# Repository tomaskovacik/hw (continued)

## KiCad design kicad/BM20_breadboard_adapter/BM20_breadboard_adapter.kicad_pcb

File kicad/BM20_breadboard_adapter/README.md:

This is directory with whole kicad project files for breadboard adapter for BM20 and BM62 bluetooth modules from Microchip

<a href="https://tomaskovacik.github.io/hw/kicad/BM20_breadboard_adapter/bom/ibom.html">interactive boom</a>

assembled or bare boards can be found on my tindie store:

<a href="https://github.com/tomaskovacik/IS2020/wiki/Upgrading-firmware-on-BM62">wiki page</a> talking about upgrading firmware on BM62 module.

<a href="https://github.com/tomaskovacik/IS2020">Arduino library</a> for this module is also available as opensource project on GitHub.

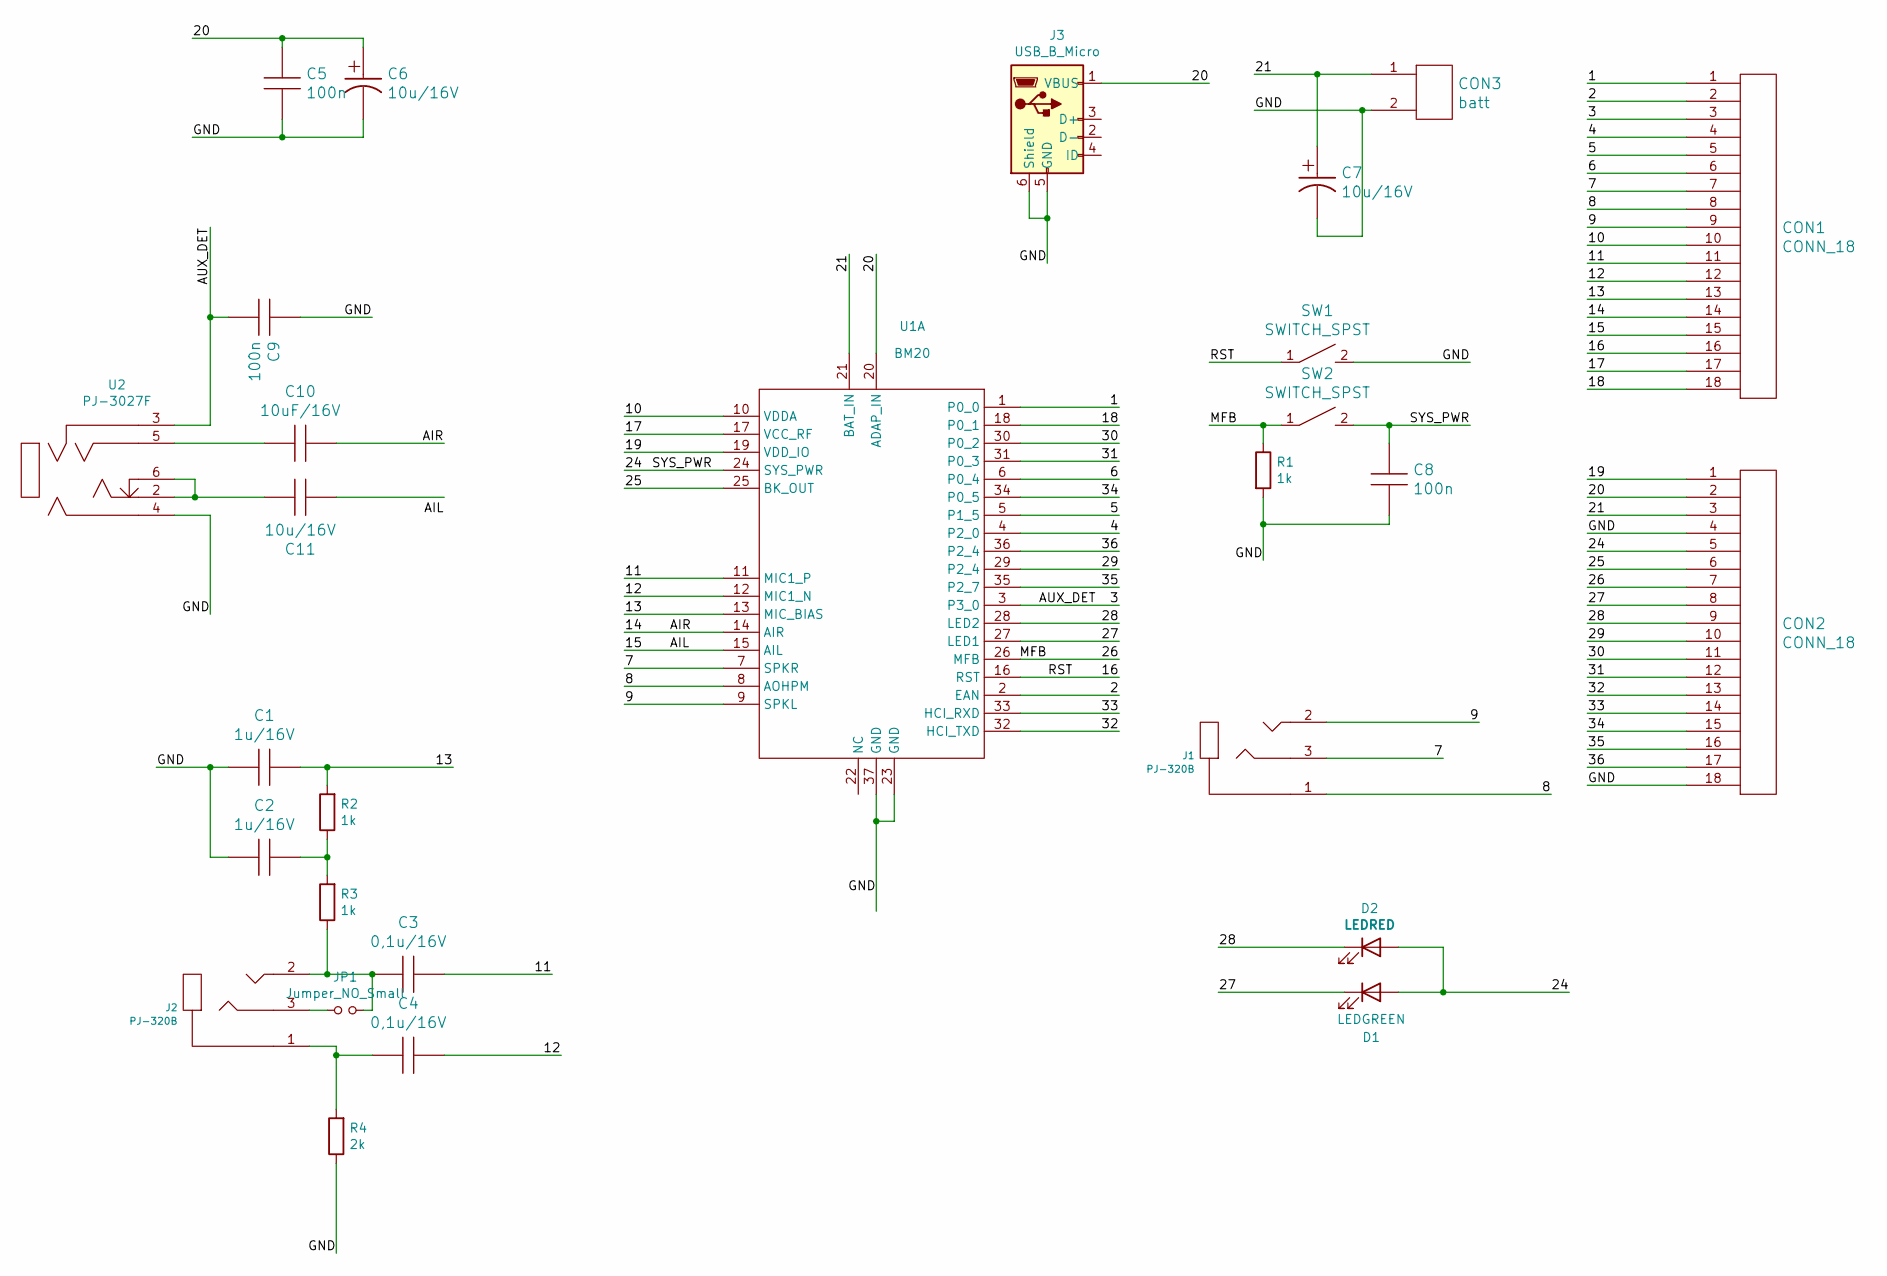
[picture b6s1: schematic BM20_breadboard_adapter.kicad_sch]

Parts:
C1, C2: 1u/16V; C_1206_HandSoldering
C3, C4: 0,1u/16V; C_1206_HandSoldering
C5, C8, C9: 100n; C_0805_HandSoldering
C6, C7, C11: 10u/16V; C_1206_HandSoldering
C10: 10uF/16V; C_1206_HandSoldering
CON1, CON2: CONN_18; Pin_Header_Straight_1x18
CON3: batt; JST_XH_B02B-XH-A_02x2.50mm_Straight
D1: LEDGREEN; LED_1206_HandSoldering
D2: LEDRED; LED_1206_HandSoldering
J1, J2: PJ-320B; 3.5mm_stereo_jack_PJ320B
J3: USB_B_Micro; USB_Micro-B
JP1: Jumper_NO_Small; SolderJumper-2_P1.3mm_Open_RoundedPad1.0x1.5mm
R1, R2, R3: 1k; R_0805_HandSoldering
R4: 2k; R_0805_HandSoldering
SW1, SW2: SWITCH_SPST; SW_SPST_FSMSM
U1: BM20; BM20_no_silk_screen_under_antena
U2: PJ-3027F; PJ-327A

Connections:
/1: CON1.1, U1.1 (P0_0)
/2: CON1.2, U1.2 (EAN)
/3: C9.2, CON1.3, U1.3 (P3_0), U2.3
/4: CON1.4, U1.4 (P2_0)
/5: CON1.5, U1.5 (P1_5)
/6: CON1.6, U1.6 (P0_4)
/7: CON1.7, J1.3, U1.7 (SPKR)
/8: CON1.8, J1.1, U1.8 (AOHPM)
/9: CON1.9, J1.2, U1.9 (SPKL)
/10: CON1.10, U1.10 (VDDA)
/11: C3.1, CON1.11, U1.11 (MIC1_P)
/12: C4.1, CON1.12, U1.12 (MIC1_N)
/13: C1.1, CON1.13, R2.2, U1.13 (MIC_BIAS)
/14: C10.1, CON1.14, U1.14 (AIR)
/15: CON1.15, U1.15 (AIL)
/16: CON1.16, SW1.1, U1.16 (RST)
/17: CON1.17, U1.17 (VCC_RF)
/18: CON1.18, U1.18 (P0_1)
/19: CON2.1, U1.19 (VDD_IO)
/20: C5.1, C6.1, CON2.2, J3.1 (VBUS), U1.20 (ADAP_IN)
/21: C7.1, CON2.3, CON3.1, U1.21 (BAT_IN)
/24: C8.1, CON2.5, D1.2 (A), D2.2 (A), SW2.2, U1.24 (SYS_PWR)
/25: CON2.6, U1.25 (BK_OUT)
/26: CON2.7, R1.1, SW2.1, U1.26 (MFB)
/27: CON2.8, D1.1 (K), U1.27 (LED1)
/28: CON2.9, D2.1 (K), U1.28 (LED2)
/29: CON2.10, U1.29 (P2_4)
/30: CON2.11, U1.30 (P0_2)
/31: CON2.12, U1.31 (P0_3)
/32: CON2.13, U1.32 (HCI_TXD)
/33: CON2.14, U1.33 (HCI_RXD)
/34: CON2.15, U1.34 (P0_5)
/35: CON2.16, U1.35 (P2_7)
/36: CON2.17, U1.36 (P2_4)
/GND: C1.2, C2.2, C5.2, C6.2, C7.2, C8.2, C9.1, CON2.4, CON2.18, CON3.2, J3.5 (GND), J3.6 (Shield), R1.2, R4.1, SW1.2, U1.23 (GND), U1.37 (GND), U2.4
unnamed: C2.1, R2.1, R3.2
unnamed: C3.2, J2.2, JP1.2, R3.1
unnamed: C4.2, J2.1, R4.2
unnamed: C10.2, U2.5
unnamed: C11.1, U2.2, U2.6
unnamed: J2.3, JP1.1

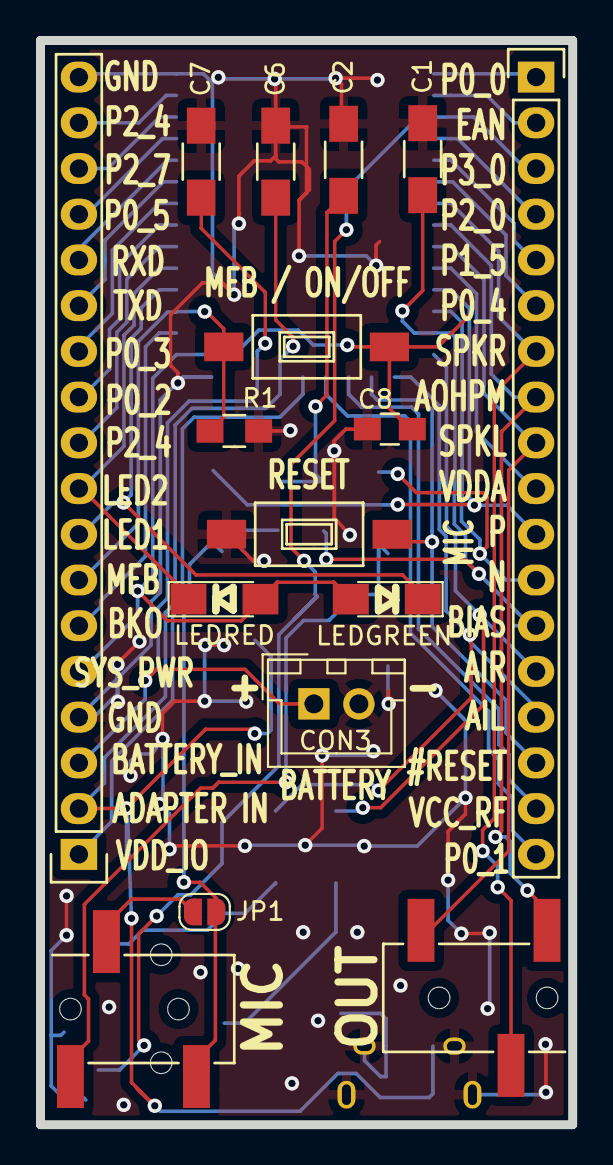
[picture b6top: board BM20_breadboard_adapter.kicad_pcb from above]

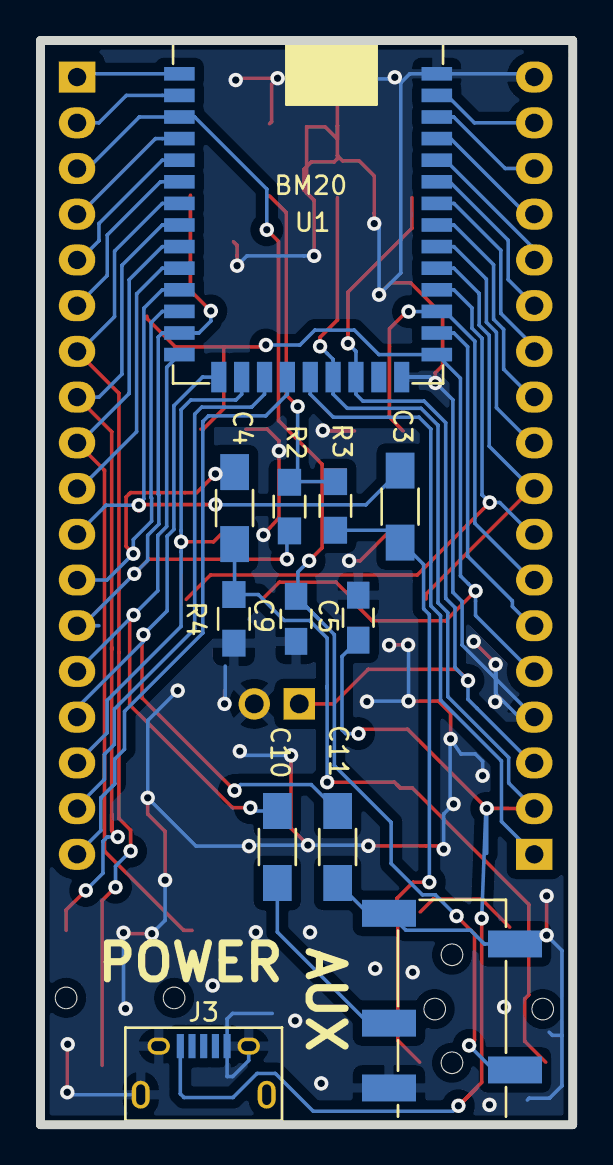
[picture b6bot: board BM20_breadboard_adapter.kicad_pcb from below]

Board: 2 copper layers, 29.6 x 60.2 mm, 28 parts (12 on the bottom side), 41 nets.

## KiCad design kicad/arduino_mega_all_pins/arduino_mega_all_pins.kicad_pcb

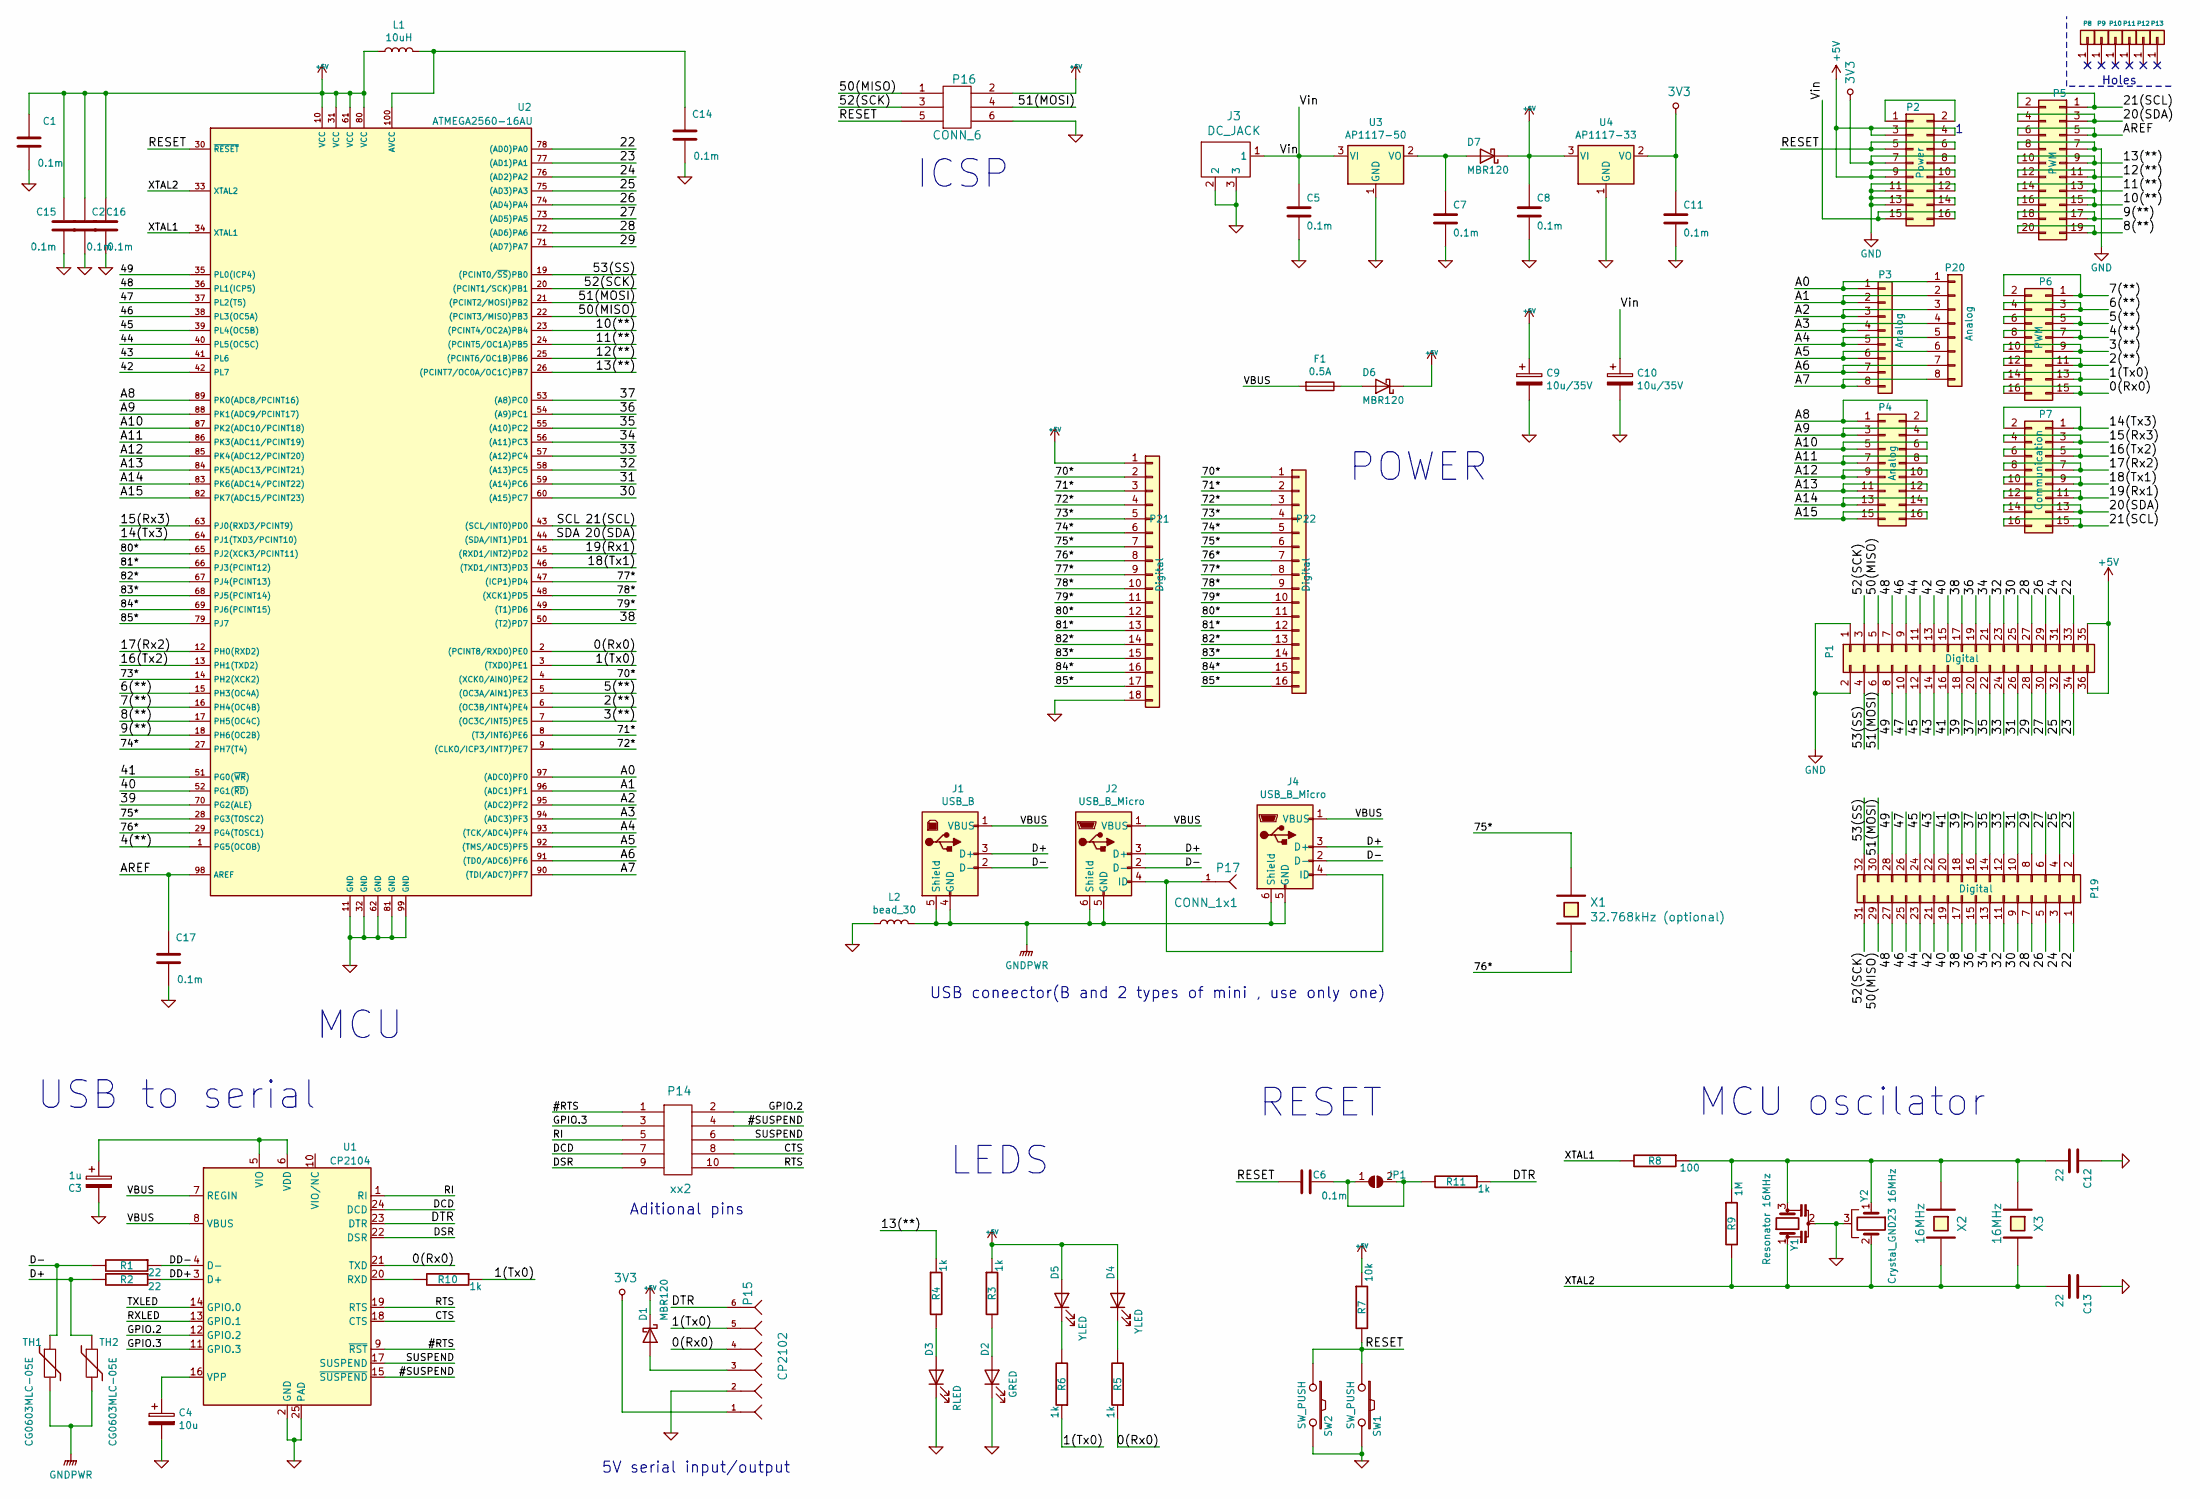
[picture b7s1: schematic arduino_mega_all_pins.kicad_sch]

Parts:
C1, C2, C5, C6, C7, C8, C11, C14, C15, C16, C17: 0.1m; C_0805_HandSoldering
C3: 1u; TantalC_SizeA_EIA-3216_Wave
C4: 10u; TantalC_SizeA_EIA-3216_Wave
C9, C10: 10u/35V; TantalC_SizeD_EIA-7343_Wave
C12, C13: 22; C_0805_HandSoldering
D1, D6, D7: MBR120; SOD-123
D2: GRED; LED-1206
D3: RLED; LED-1206
D4, D5: YLED; LED-1206
F1: 0.5A; Fuse_SMD1206_Wave
J1: USB_B
J2: USB_B_Micro; USB_Micro-B
J3: DC_JACK; JACK_ALIM
J4: USB_B_Micro; AB2_USB_MICRO_SMD
JP1: SolderJumper_2_Bridged; SolderJumper-2_P1.3mm_Open_RoundedPad1.0x1.5mm
L1: 10uH; Choke_SMD_1206_Standard
L2: bead_30; Choke_SMD_1206_Standard
P1: Digital; Socket_Strip_Arduino_2x18
P2: Power; Pin_Header_Straight_2x08
P3, P20: Analog; Pin_Header_Straight_1x08
P4: Analog; Pin_Header_Straight_2x08
P5: PWM; Pin_Header_Straight_2x10
P6: PWM; Pin_Header_Straight_2x08
P7: Communication; Pin_Header_Straight_2x08
P8, P9, P10, P11, P12, P13: CONN_01X01; Arduino_1pin
P14: xx2; Pin_Header_Straight_2x05
P15: CP2102; Pin_Header_Straight_1x06
P16: CONN_6; Pin_Header_Straight_2x03
P17: CONN_1x1; Pin_Header_Straight_1x01
P19: Digital; Pin_Header_Straight_2x16
P21: Digital; Pin_Header_Straight_1x18
P22: Digital; Pin_Header_Straight_1x16
R1, R2: 22; R_0805_HandSoldering
R3, R4, R5, R6, R10, R11: 1k; R_0805_HandSoldering
R7: 10k; R_0805_HandSoldering
R8: 100; R_0805_HandSoldering
R9: 1M; R_0805_HandSoldering
SW1, SW2: SW_PUSH; 3x6x2.5mm_tact_switch
TH1, TH2: CG0603MLC-05E; R_0603_HandSoldering
U1: CP2104; QFN-24-1EP_4x4mm_Pitch0.5mm
U2: ATMEGA2560-16AU; TQFP-100_14x14mm_Pitch0.5mm
U3: AP1117-50; AB2_SOT223
U4: AP1117-33; AB2_SOT223
X1: 32.768kHz (optional); Crystal_Round_Horizontal_3mm_BigPad
X2: 16MHz; Crystal_HC49-U_Vertical
X3: 16MHz; Q_49U3HMS
Y1: Resonator 16MHz; MURATA_CSTCE_V53
Y2: Crystal_GND23 16MHz; CRYSTAL_3225

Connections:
3V3: C11.1, P2.7, P2.8, P15.1, U4.2 (VO)
+5V: C1.2, C2.2, C8.1, C9.1, C15.2, C16.2, D1.1 (K), D4.2 (A), D5.2 (A), D6.1 (K), D7.1 (K), L1.1, P1.35, P1.36, P2.3, P2.4, P2.9, P2.10, P16.2, P21.1, R3.1, R7.1, U2.10 (VCC), U2.31 (VCC), U2.61 (VCC), U2.80 (VCC), U4.3 (VI)
/0(Rx0): P6.15, P6.16, P15.4, R5.1, U1.21 (TXD), U2.2 ((PCINT8/RXD0)PE0)
/1(Tx0): P6.13, P6.14, P15.5, R6.1, R10.1, U2.3 ((TXD0)PE1)
/2(**): P6.11, P6.12, U2.6 ((OC3B/INT4)PE4)
/3(**): P6.9, P6.10, U2.7 ((OC3C/INT5)PE5)
/4(**): P6.7, P6.8, U2.1 (PG5(OCOB))
/5(**): P6.5, P6.6, U2.5 ((OC3A/AIN1)PE3)
/6(**): P6.3, P6.4, U2.15 (PH3(OC4A))
/7(**): P6.1, P6.2, U2.16 (PH4(OC4B))
/8(**): P5.19, P5.20, U2.17 (PH5(OC4C))
/9(**): P5.17, P5.18, U2.18 (PH6(OC2B))
/10(**): P5.15, P5.16, U2.23 ((PCINT4/OC2A)PB4)
/11(**): P5.13, P5.14, U2.24 ((PCINT5/OC1A)PB5)
/12(**): P5.11, P5.12, U2.25 ((PCINT6/OC1B)PB6)
/13(**): P5.9, P5.10, R4.1, U2.26 ((PCINT7/OC0A/OC1C)PB7)
/14(Tx3): P7.1, P7.2, U2.64 (PJ1(TXD3/PCINT10))
/15(Rx3): P7.3, P7.4, U2.63 (PJ0(RXD3/PCINT9))
/16(Tx2): P7.5, P7.6, U2.13 (PH1(TXD2))
/17(Rx2): P7.7, P7.8, U2.12 (PH0(RXD2))
/18(Tx1): P7.9, P7.10, U2.46 ((TXD1/INT3)PD3)
/19(Rx1): P7.11, P7.12, U2.45 ((RXD1/INT2)PD2)
/20(SDA): P5.3, P5.4, P7.13, P7.14, U2.44 ((SDA/INT1)PD1)
/21(SCL): P5.1, P5.2, P7.15, P7.16, U2.43 ((SCL/INT0)PD0)
/22: P1.33, P19.1, U2.78 ((AD0)PA0)
/23: P1.34, P19.2, U2.77 ((AD1)PA1)
/24: P1.31, P19.3, U2.76 ((AD2)PA2)
/25: P1.32, P19.4, U2.75 ((AD3)PA3)
/26: P1.29, P19.5, U2.74 ((AD4)PA4)
/27: P1.30, P19.6, U2.73 ((AD5)PA5)
/28: P1.27, P19.7, U2.72 ((AD6)PA6)
/29: P1.28, P19.8, U2.71 ((AD7)PA7)
/30: P1.25, P19.9, U2.60 ((A15)PC7)
/31: P1.26, P19.10, U2.59 ((A14)PC6)
/32: P1.23, P19.11, U2.58 ((A13)PC5)
/33: P1.24, P19.12, U2.57 ((A12)PC4)
/34: P1.21, P19.13, U2.56 ((A11)PC3)
/35: P1.22, P19.14, U2.55 ((A10)PC2)
/36: P1.19, P19.15, U2.54 ((A9)PC1)
/37: P1.20, P19.16, U2.53 ((A8)PC0)
/38: P1.17, P19.17, U2.50 ((T2)PD7)
/39: P1.18, P19.18, U2.70 (PG2(ALE))
/40: P1.15, P19.19, U2.52 (PG1(~RD~))
/41: P1.16, P19.20, U2.51 (PG0(~WR~))
/42: P1.13, P19.21, U2.42 (PL7)
/43: P1.14, P19.22, U2.41 (PL6)
/44: P1.11, P19.23, U2.40 (PL5(OC5C))
/45: P1.12, P19.24, U2.39 (PL4(OC5B))
/46: P1.9, P19.25, U2.38 (PL3(OC5A))
/47: P1.10, P19.26, U2.37 (PL2(T5))
/48: P1.7, P19.27, U2.36 (PL1(ICP5))
/49: P1.8, P19.28, U2.35 (PL0(ICP4))
/50(MISO): P1.5, P16.1, P19.29, U2.22 ((PCINT3/MISO)PB3)
/51(MOSI): P1.6, P16.4, P19.30, U2.21 ((PCINT2/MOSI)PB2)
/52(SCK): P1.3, P16.3, P19.31, U2.20 ((PCINT1/SCK)PB1)
/53(SS): P1.4, P19.32, U2.19 ((PCINT0/~SS~)PB0)
/70*: P21.2, P22.1, U2.4 ((XCK0/AIN0)PE2)
/71*: P21.3, P22.2, U2.8 ((T3/INT6)PE6)
/72*: P21.4, P22.3, U2.9 ((CLKO/ICP3/INT7)PE7)
/73*: P21.5, P22.4, U2.14 (PH2(XCK2))
/74*: P21.6, P22.5, U2.27 (PH7(T4))
/75*: P21.7, P22.6, U2.28 (PG3(TOSC2)), X1.1
/76*: P21.8, P22.7, U2.29 (PG4(TOSC1)), X1.2
/77*: P21.9, P22.8, U2.47 ((ICP1)PD4)
/78*: P21.10, P22.9, U2.48 ((XCK1)PD5)
/79*: P21.11, P22.10, U2.49 ((T1)PD6)
/80*: P21.12, P22.11, U2.65 (PJ2(XCK3/PCINT11))
/81*: P21.13, P22.12, U2.66 (PJ3(PCINT12))
/82*: P21.14, P22.13, U2.67 (PJ4(PCINT13))
/83*: P21.15, P22.14, U2.68 (PJ5(PCINT14))
/84*: P21.16, P22.15, U2.69 (PJ6(PCINT15))
/85*: P21.17, P22.16, U2.79 (PJ7)
/#RTS: P14.1, U1.9 (~RST)
/#SUSPEND: P14.4, U1.15 (~SUSPEND)
/A0: P3.1, P20.1, U2.97 ((ADC0)PF0)
/A1: P3.2, P20.2, U2.96 ((ADC1)PF1)
/A2: P3.3, P20.3, U2.95 ((ADC2)PF2)
/A3: P3.4, P20.4, U2.94 ((ADC3)PF3)
/A4: P3.5, P20.5, U2.93 ((TCK/ADC4)PF4)
/A5: P3.6, P20.6, U2.92 ((TMS/ADC5)PF5)
/A6: P3.7, P20.7, U2.91 ((TD0/ADC6)PF6)
/A7: P3.8, P20.8, U2.90 ((TDI/ADC7)PF7)
/A8: P4.1, P4.2, U2.89 (PK0(ADC8/PCINT16))
/A9: P4.3, P4.4, U2.88 (PK1(ADC9/PCINT17))
/A10: P4.5, P4.6, U2.87 (PK2(ADC10/PCINT18))
/A11: P4.7, P4.8, U2.86 (PK3(ADC11/PCINT19))
/A12: P4.9, P4.10, U2.85 (PK4(ADC12/PCINT20))
/A13: P4.11, P4.12, U2.84 (PK5(ADC13/PCINT21))
/A14: P4.13, P4.14, U2.83 (PK6(ADC14/PCINT22))
/A15: P4.15, P4.16, U2.82 (PK7(ADC15/PCINT23))
/AREF: C17.2, P5.5, P5.6, U2.98 (AREF)
/CTS: P14.8, U1.18 (CTS)
/D+: J1.3 (D+), J2.3 (D+), J4.3 (D+), R2.2, TH2.1
/D-: J1.2 (D-), J2.2 (D-), J4.2 (D-), R1.2, TH1.1
/DCD: P14.7, U1.24 (DCD)
/DD+: R2.1, U1.3 (D+)
/DD-: R1.1, U1.4 (D-)
/DSR: P14.9, U1.22 (DSR)
/DTR: P15.6, R11.1, U1.23 (DTR)
/GPIO.2: P14.2, U1.12 (GPIO.2)
/GPIO.3: P14.3, U1.11 (GPIO.3)
/RESET: C6.1, P2.5, P2.6, P16.5, R7.2, SW1.1, SW2.1, U2.30 (~RESET)
/RI: P14.5, U1.1 (RI)
/RTS: P14.10, U1.19 (RTS)
/SUSPEND: P14.6, U1.17 (SUSPEND)
/VBUS: F1.2, J1.1 (VBUS), J2.1 (VBUS), J4.1 (VBUS), U1.7 (REGIN), U1.8 (VBUS)
/Vin: C5.1, C10.1, J3.1, P2.15, P2.16, U3.3 (VI)
/XTAL1: R8.2, U2.34 (XTAL1)
/XTAL2: C13.2, R9.2, U2.33 (XTAL2), X2.2, X3.2, Y1.1, Y2.2
GND: C1.1, C2.1, C3.2, C4.2, C5.2, C7.2, C8.2, C9.2, C10.2, C11.2, C12.1, C13.1, C14.1, C15.1, C16.1, C17.1, D2.1 (K), D3.1 (K), J3.2, J3.3, L2.1, P1.1, P1.2, P2.11, P2.12, P2.13, P2.14, P5.7, P5.8, P15.2, P16.6, P21.18, SW1.2, SW2.2, U1.2 (GND), U1.25 (PAD), U2.11 (GND), U2.32 (GND), U2.62 (GND), U2.81 (GND), U2.99 (GND), U3.1 (GND), U4.1 (GND), Y1.2, Y2.3
GNDPWR: J1.4 (GND), J1.5 (Shield), J2.5 (GND), J2.6 (Shield), J4.5 (GND), J4.6 (Shield), L2.2, TH1.2, TH2.2
unnamed: C3.1, U1.5 (VIO), U1.6 (VDD)
unnamed: C4.1, U1.16 (VPP)
unnamed: C6.2, JP1.1 (A), JP1.2 (B), R11.2
unnamed: C7.1, D7.2 (A), U3.2 (VO)
unnamed: C12.2, R8.1, R9.1, X2.1, X3.1, Y1.3, Y2.1
unnamed: C14.2, L1.2, U2.100 (AVCC)
unnamed: D1.2 (A), P15.3
unnamed: D2.2 (A), R3.2
unnamed: D3.2 (A), R4.2
unnamed: D4.1 (K), R5.2
unnamed: D5.1 (K), R6.2
unnamed: D6.2 (A), F1.1
unnamed: J2.4 (ID), J4.4 (ID), P17.1
unnamed: P2.1, P2.2
unnamed: R10.2, U1.20 (RXD)

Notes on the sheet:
USB to serial
MCU
5V serial input/output
Aditional pins
ICSP
USB coneector(B and 2 types of mini , use only one)
LEDS
POWER
RESET
MCU oscilator
Holes

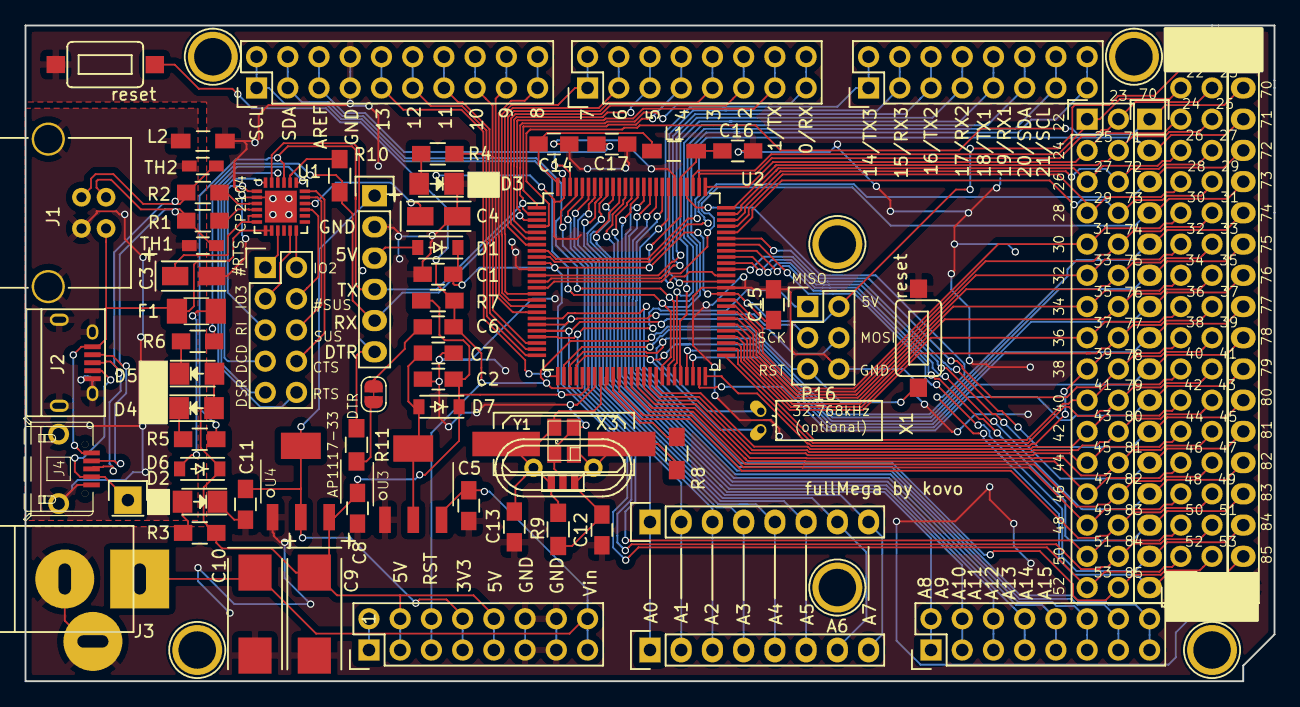
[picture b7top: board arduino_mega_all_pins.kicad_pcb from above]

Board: 2 copper layers, 101.6 x 53.3 mm, 77 parts (0 on the bottom side), 126 nets.

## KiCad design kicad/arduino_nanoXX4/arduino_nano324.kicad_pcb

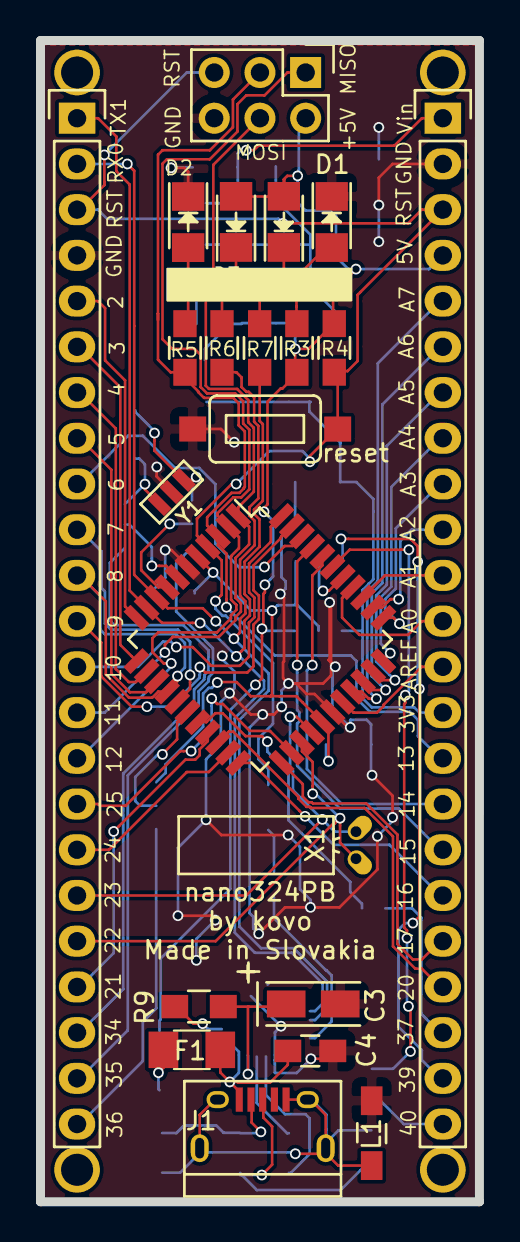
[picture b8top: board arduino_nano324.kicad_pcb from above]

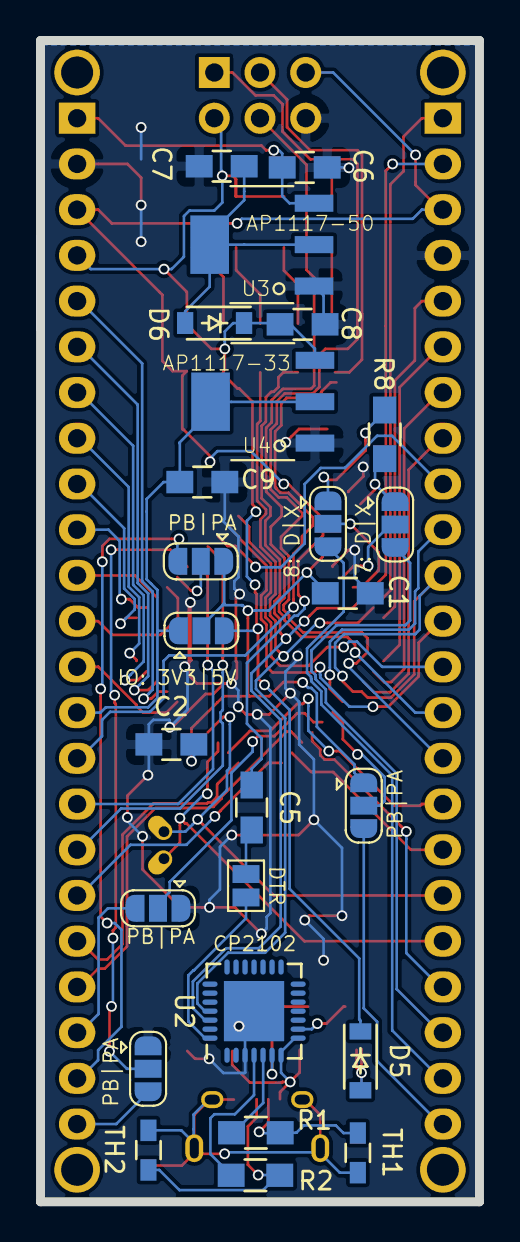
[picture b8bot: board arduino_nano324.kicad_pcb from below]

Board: 2 copper layers, 24.4 x 64.5 mm, 51 parts (25 on the bottom side), 69 nets.

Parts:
C1, C2, C4, C5, C6, C7, C8, C9: 0.1m; C_0805_HandSoldering
C3: 1u; TantalC_SizeA_EIA-3216_Wave
D1: GRED; LED-1206
D2: GLED; LED-1206
D3, D4: YLED; LED-1206
D5, D6: MBR120; SOD-123
F1: Fuse; Fuse_SMD1206_Wave
J1: USB_B_Micro; USB_Micro-B
JP1, JP2, JP3, JP4, JP5, JP6: Jumper_3_Open; SolderJumper-3_P1.3mm_Open_RoundedPad1.0x1.5mm
JP7: VIO; SolderJumper-3_P1.3mm_Open_RoundedPad1.0x1.5mm
JP9: Jumper; SolderJumper-2_P1.3mm_Open_Pad1.0x1.5mm
L1: ferite_bead; Choke_SMD_1206_Standard
P1: Digital; Pin_Header_Straight_1x23
P2: Analog; Pin_Header_Straight_1x23
P3, P4, P5, P6: CONN_01X01; 1pin_Nano
P7: CONN_6; Pin_Header_Straight_2x03
R1, R2: 22; R_0805_HandSoldering
R3, R5, R6, R7: 1k; R_0805_HandSoldering
R4, R9: 10k; R_0805_HandSoldering
R8: 1M; R_0805_HandSoldering
SW1: SW_PUSH; 3x6x2.5mm_tact_switch
TH1, TH2: MLC-05E; R_0603_HandSoldering
U1: ATMEGA324PB-AU; TQFP-44_10x10mm_Pitch0.8mm
U2: CP2102N-A01-GQFN28; QFN-28-1EP_5x5mm_Pitch0.5mm
U3: AP1117-50; AB2_SOT223
U4: AP1117-33; AB2_SOT223
X1: CRYSTAL; Crystal_Round_Horizontal_3mm_BigPad
Y1: 16Mhz; MURATA_CSTCE_V53

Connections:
3V3: C9.1, JP7.1, P2.14, U4.2
+5V: C8.1, D3.2, D4.2, D5.1, D6.1, JP7.3, P2.4, P7.2, R3.1, R4.1, U4.3
/0(Rx): P1.2, R6.1, U1.9, U2.26
/1(Tx): P1.1, R7.1, U1.10, U2.25
/2: P1.5, U1.11
/3(**): P1.6, U1.12
/4: P1.7, U1.13
/5(**): P1.8, U1.14
/6(**): P1.9, U1.42
/7: JP1.2, U1.7
/8: JP2.2, U1.8
/9(**): P1.12, U1.43
/10(**/SS): P1.13, U1.44
/11(**/MOSI): P1.14, P7.4, U1.1
/12(MISO): P1.15, P7.1, U1.2
/13(SCK): P2.15, P7.3, R5.1, U1.3
/17: JP3.2, U1.17
/18: JP4.2, U1.18
/38: JP5.2, U1.38
/39: JP6.2, U1.39
/#RST: R9.1, U2.9
/A0: P2.12, U1.37
/A1: P2.11, U1.36
/A2: P2.10, U1.35
/A3: P2.9, U1.34
/A4: P2.8, U1.33
/A5: P2.7, U1.32
/A6: P2.6, U1.31
/A7: P2.5, U1.30
/AREF: P2.13, U1.29
/D7: P1.10, U1.16
/D8: P1.11, U1.15
/D14: P2.16, U1.40
/D15: P2.17, U1.41
/D16: P2.18, U1.22
/D17: P2.19, U1.23
/D20: P2.20, U1.20
/D21: P1.20, U1.19
/D22: P1.19, U1.25, X1.1
/D23: P1.18, U1.26, X1.2
/D32: P1.17, U1.21
/D33: P1.16, U1.24
/D34: JP1.3, P1.21
/D35: JP2.3, P1.22
/D36: JP3.3, P1.23
/D37: JP4.3, P2.21
/D39: JP5.3, P2.22
/D40: JP6.3, P2.23
/D+: J1.3, R2.2, TH2.1
/D-: J1.2, R1.2, TH1.1
/DD+: R2.1, U2.4
/DD-: R1.1, U2.5
/DTR: JP9.2, U2.28
/Reset: C5.1, P1.3, P2.3, P7.5, R4.2, SW1.1, U1.4
/VBUS: C4.1, F1.2, J1.1, U2.7, U2.8
/Vin: C6.1, P2.1, U3.3
/XTAL1: JP2.1, R8.1, Y1.3
/XTAL2: JP1.1, R8.2, Y1.1
GND: C1.1, C2.1, C3.2, C4.2, C6.2, C7.2, C8.2, C9.2, D1.1, D2.1, JP4.1, JP6.1, L1.1, P1.4, P2.2, P7.6, SW1.2, U1.6, U1.28, U2.3, U2.29, U3.1, U4.1, Y1.2
GNDPWR: J1.5, J1.6, L1.2, TH1.2, TH2.2
unnamed: C3.1, R9.2, U2.6
unnamed: C5.2, JP9.1
unnamed: C7.1, D6.2, U3.2
unnamed: D1.2, R3.2
unnamed: D2.2, R5.2
unnamed: D3.1, R6.2
unnamed: D4.1, R7.2
unnamed: D5.2, F1.1
VCC: C1.2, C2.2, JP3.1, JP5.1, JP7.2, U1.5, U1.27

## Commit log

2017-09-11 moved to kicad-library repo
2017-09-11 remove XS3868 board support
2017-09-11 XS3868 separated board
2017-09-11 pics
2017-11-28 schematics in pdf
2018-03-21 removed same files, md5sum was exactly same
2018-04-13 to fcking much changes to commit it separatly, lets go with everything in one commit, git will love me for sure :D
2018-04-13 typo
2018-04-13 schematics export
2018-04-25 license
2018-05-02 schematics
2018-05-03 schematics for version 1.0 of PCB
2018-05-04 v1 historical files
2018-05-07 move v1 to old dir
2018-05-07 BOM fo v1
2018-05-07 fix v1
2018-05-16 new version
2018-06-01 attempt to revers engeneer schematics of westfamilia astm12 506005
2018-06-01 zipped gimp file
2018-06-08 remove dasmx140 from girhub
2018-06-08 remove unused test dir
2018-06-19 change names to accomodate disasmx req.
2018-06-19 sym files to disamx for bin file from prev. comment
2018-06-19 pin mapping for audi concert to 68hc05b32
2018-06-19 script which add comments to asm
2018-06-19 new asm files with threading and correct start at 0x400
2018-06-19 default motorola 68HC05B32 symbol file for dasmx14
2018-06-19 asm's with comments
2018-06-20 fix port bit name identify
2018-06-20 rename *.rom to *..bin
2018-06-20 disasm.sh shell script
2018-06-20 slave pins
2018-06-20 change symbol to byte for ram/eeprom/bootstrap in symbol files
2018-06-20 symbol replaced with byte
2018-06-21 script for generating full memory dump from eeprom and rom of motorola MC68HC05B32
2018-06-21 asm of full memory created with gen_full_mem.sh with and without comments
2018-06-21 datasheets for motorola mcus
2018-06-21 datasheet for OKI MSM6688L, recoder for TP in audi concert1/chorus1
2018-06-21 add reserved memory slots
2018-06-21 change case states to exact words without asterix to avoid wrong coments
2018-06-21 dissasembled without threads
2018-06-21 no threads
2018-07-10 readme
2018-08-06 readme update
2018-09-21 moved to separed repository audi_concert1_chorus1_volume_fix
2018-09-27 updated version
2018-10-02 udpated to version 2.1
2018-10-02 pictures of 2.0 version
2018-10-02 move version 1.0 files to dir 1.0
2018-10-02 readme update v2.0
2018-10-29 version 2.0
2018-11-04 info about v1.2 version of module
2018-12-14 assamble plan
2018-12-14 version 3.0
2018-12-14 rename
2019-03-01 remove PROD dir
2019-03-01 move
2019-03-01 assamle plans
2019-03-01 old assamble plansold/F-6888_breakaout_adapter-assable_plan.png
2019-03-01 misc
2019-05-10 init nano PB
2019-05-13 rm gerbers zip
2019-05-13 assemble plan has its own dir now
2019-05-13 KIT picture for tindie.com/stores/tomaskovacik/
2019-05-13 BOM in openoffice ODS
2019-05-13 pictures of PCB and assembled unit
2019-05-13 clean up
2019-05-13 cleaup
2019-05-13 nanoPB pinout in pdf
2019-05-13 new pics
2019-05-13 croped pictures
2019-05-13 picture with solder jumper explenation
2019-05-20 scl1->scl0
2019-05-20 reset pin info on pinout pics
2019-05-20 Create LICENSE.md
    arduino nano is licensed under CC SA
2019-05-23 pins 20,21 break out
2019-05-30 pictures
2019-05-30 Update README.md
    added pictures
2019-05-30 additional files of kicad project for F3188 adapter
2019-05-30 update files of kicad project for F3188 adapter
2019-05-30 readme update correct schematics file
2019-05-30 remove 1.0 pictures
2019-05-30 move pics from 2.0 to pics
2019-05-30 clear duplicated files
2019-05-30 remove old pics
2019-05-30 update xs3868 kicad project files
2019-07-01 init commit
2019-07-23 arduino nano pin name compitible breadboard compatible board using atmega324PA and compatible chips
2019-07-23 arduino mega pin compatible board with atmega2560 chips and exposed all missing pins compared to original mega
2019-07-26 v2, buttons, mic support, 3leds usb port
2019-08-29 remove obsolete project for 42mm led car interior bulb replacement
2019-08-29 remove useless projects
2019-08-29 cleaning
2019-08-29 remove old projects
2019-08-29 cleanup
2019-11-30 init public commit
2020-06-19 interctive bom
2020-07-02 files for version 1.0
2020-07-02 pintout and assemble plan for v2.0
2020-07-02 pcb v2.0
2020-07-02 schematics v2.0
2020-07-16 interactive bom for v2.0
2020-07-16 move to lfs
2020-07-16 interactive bom for v1
2020-07-16 new schematic format
2020-07-16 v1 schematics in new format, for hist. reasons
2020-07-16 remove prod dir with files
2020-07-16 reove sym-lib-table
2020-07-23 new module hw
2020-07-23 init readme with interactive boom
2020-10-05 atmegax8_with_F-3188/
    cd changer with BK8000L module
2020-10-05 changes to BM20 version, not finished yet
2020-10-05 changes to bt version, but it is not good, do not use this setup
2020-10-05 schematics in new file format
2020-10-05 using BK8000L works
2020-10-06 revert to 3188 name which is proper
2020-10-06 schematics in new format
2020-10-06 moved to kicad_sch format
2020-10-06 rename conn4 to 7805
2020-10-06 ibom schematics
2020-10-06 delete improper ibom.html file
    It belongs to bk8000l version
2020-10-06 moved vwcdavr hw file to https://github.com/tomaskovacik/vwcdavr/HW
2020-11-09 fake xenon autolevel
2020-11-09 pictures of assembled units
2021-04-20 bm64 adapter
2021-05-08 BM83adapter
2021-05-08 bm83pictures
2021-05-30 remove plot
2021-05-30 interactive bom
2021-11-15 headlight_washer_pump_controler
2021-11-15 comment about R1
2021-11-15 update BM83 footprint on board!
2021-11-15 wiper_motor_control_board
2021-11-15 fake_xenon4_update
2021-11-15 bm71_MODULE
2022-12-28 fixies
2022-12-28 new kicad file names
2022-12-28 gerbers
